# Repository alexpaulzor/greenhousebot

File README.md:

# greenhousebot

Controller for a greenhouse: temperature/humidity-driven **misters** (12 V valve),
**fans** (mains, switched externally) — an **exhaust/vent** fan and an **interior
circulation** fan on independent relays — and a **window** (12 V linear actuator via
H-bridge), on a **Raspberry Pi Pico 2 W** with a 1602 LCD + 3 buttons.

## Architecture (current)

- **Pico 2 W** brain; pre-made modules for relay / H-bridge / buck / LCD / AHT21 sensor.
- **No PCB — solderless terminal-block build.** The circuit is power-rail fan-out + a
  2-wire I2C bus, so a **Pico screw-terminal expander** + **Wago lever-nuts** do the
  interconnect. Nothing sensitive is soldered. See **[docs/WIRING.md](docs/WIRING.md)**.
- **Mains AC stays in mains-rated J-boxes**: a **3-channel 3.3 V relay board** (valve /
  vent fan / circ fan; mechanical, 10 A @ 125 V — no SSR) lives in a **relay J-box**, with a
  stacked **mains J-box** holding the incoming mains + two switched fan outlets. Only the
  relay coil side + the 12 V DC valve feed cross in from the logic box.
- **Single 12 V 5 A PSU** → valve + H-bridge + a buck to 5 V for the Pico.
- **Sensors**: **two AHT21** (I2C 0x38) — indoor (I2C0, with the LCD) + outdoor (I2C1, own
  bus, long run). **LCD run at 3.3 V** → whole I2C bus is 3.3 V, **no level shifter**.
- **Buttons**: three panel-mount momentaries; each press **cycles** its actuator's mode
  (window / fans / mister). Wire in via screw terminals.
- **Housing**: a purchased sealed plastic bin, mounted outdoors by the door, one gland.
  (Swappable LCD faceplate + MakerBeam module mounts are deferred TODOs.)

## Documents (start here)

| Doc | What |
|-----|------|
| [docs/CONNECTIONS.md](docs/CONNECTIONS.md) | **Logical pin-to-pin** (mermaid + table) — start here |
| [docs/WIRING.md](docs/WIRING.md) | **Solderless build guide** (buses, terminals, bring-up) |
| [docs/BOM.md](docs/BOM.md) | Bill of materials + sizing |
| [docs/PINOUT.md](docs/PINOUT.md) | Pico GPIO assignments (single source of truth) |
| [firmware/README.md](firmware/README.md) | **Firmware** modules, flashing, web API |

## Status

- [x] BOM finalized (2× AHT21, no level shifter, 12 V 5 A, terminal-block build)
- [x] Pin mappings finalized (two I2C buses for indoor + outdoor sensors)
- [x] Connectivity / circuit (logical) — `docs/CONNECTIONS.md`
- [x] Interconnect decided: **no PCB**, solderless terminal blocks — `docs/WIRING.md`
- [x] Firmware — button mode-cycles, LCD, LAN web control + scrape API, bounded flash
  datalog, **live automation** (per-actuator AUTO/manual modes driven by `control.py`),
  a **web chart** of the logged data, and **web-adjustable settings** (setpoints/timings
  tunable from the page, persisted to flash). 68 host tests passing. See `firmware/README.md`.

### Deferred TODOs
- Threshold **hysteresis** (deadbands) if the logs show actuator chatter at a setpoint.
- Laser-cut swappable LCD/button faceplate (1602 now, 2004 later).
- MakerBeam (15×15) module-mount plates.
- Confirm the window actuator's internal endstops (else use spare GP13/14/15).

---

## `pcb/` + `kicad/` — superseded PCB tooling (reference only)

An earlier direction was a milled single-sided carrier PCB. We **dropped the PCB** once
the parts became modular/socketed (a breakout is all that's needed). This tooling is kept
as a **learning artifact**, not part of the build:

- `pcb/*.py` — a from-scratch, reproducible PCB toolchain (footprints → placement →
  netlist → maze router → **polygon DRC gate** → GRBL post). The DRC refused to emit
  shorting G-code, which is what surfaced that a dense single-sided board was marginal.
- `kicad/greenhousebot.kicad_pcb` — a pcbnew-API-generated board. **Note:** it opens via
  the CLI/DRC but **crashes the KiCad GUI** because its custom Pico footprint isn't backed
  by a library table entry (a known limitation of API-built boards). Not worth fixing since
  the PCB is dropped; don't rely on these files for the build.

`CIRCUIT.md` and `KICAD_SETUP.md` document that earlier PCB path.

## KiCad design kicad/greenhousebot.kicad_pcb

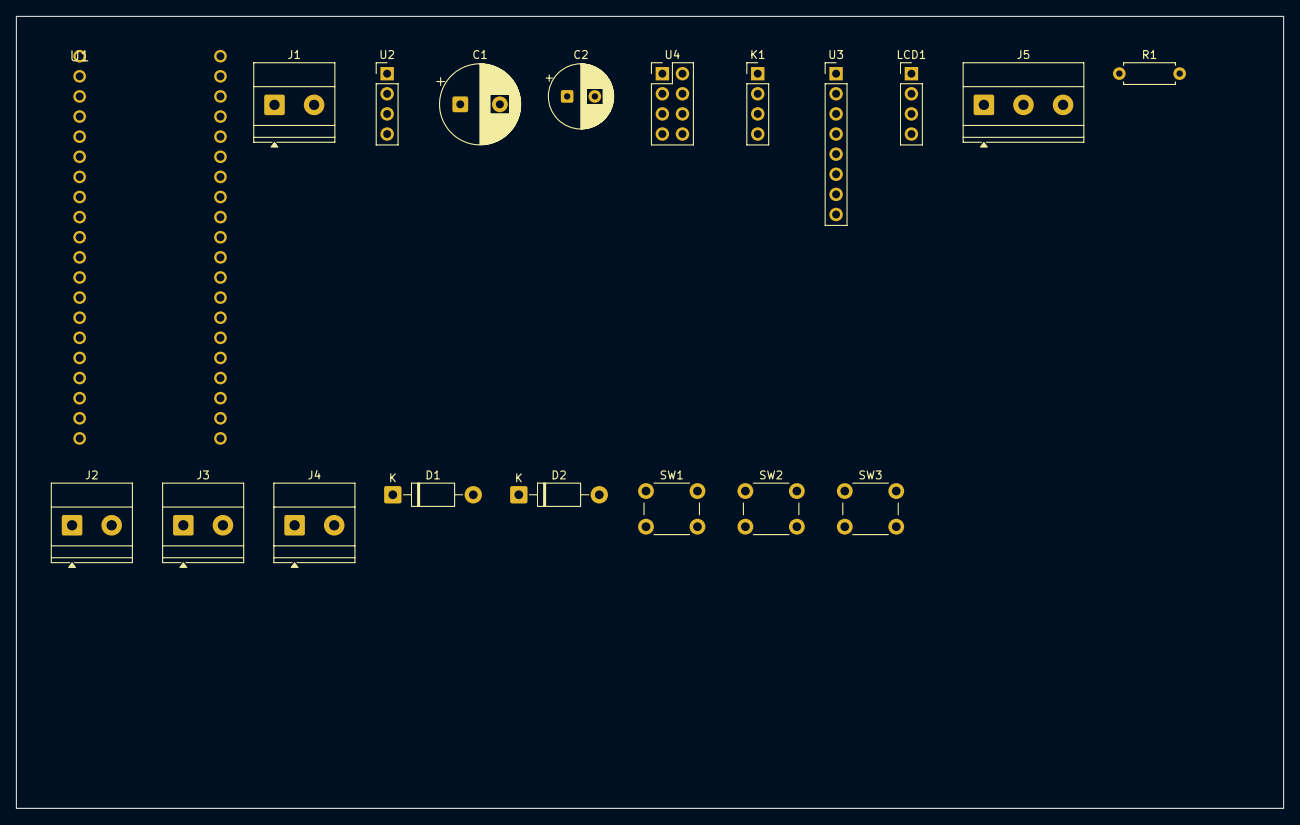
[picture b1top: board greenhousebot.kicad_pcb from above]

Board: 2 copper layers, 160.0 x 100.0 mm, 19 parts (0 on the bottom side), 20 nets, no tracks yet.

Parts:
C1: 1000uF; CP_Radial_D10.0mm_P5.00mm
C2: 470uF; CP_Radial_D8.0mm_P3.50mm
D1: SS14; D_DO-41_SOD81_P10.16mm_Horizontal
D2: 1N4007; D_DO-41_SOD81_P10.16mm_Horizontal
J1: 12V_IN; TerminalBlock_Phoenix_MKDS-1,5-2_1x02_P5.00mm_Horizontal
J2: VALVE; TerminalBlock_Phoenix_MKDS-1,5-2_1x02_P5.00mm_Horizontal
J3: ACTUATOR; TerminalBlock_Phoenix_MKDS-1,5-2_1x02_P5.00mm_Horizontal
J4: MAINS_TRIG; TerminalBlock_Phoenix_MKDS-1,5-2_1x02_P5.00mm_Horizontal
J5: DHT22; TerminalBlock_Phoenix_MKDS-1,5-3_1x03_P5.00mm_Horizontal
K1: Relay2ch; PinHeader_1x04_P2.54mm_Vertical
LCD1: LCD_I2C; PinHeader_1x04_P2.54mm_Vertical
R1: 10k; R_Axial_DIN0207_L6.3mm_D2.5mm_P7.62mm_Horizontal
SW1: BTN-; SW_PUSH_6mm
SW2: BTN_OK; SW_PUSH_6mm
SW3: BTN+; SW_PUSH_6mm
U1: Pico_2W
U2: Buck_5V; PinHeader_1x04_P2.54mm_Vertical
U3: BTS7960; PinHeader_1x08_P2.54mm_Vertical
U4: BSS138_LS; PinHeader_2x04_P2.54mm_Vertical

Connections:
3V3: J5.1, K1.1, R1.1, U1.36, U4.2
5V_BUCK: C2.1, D1.2, LCD1.2, U2.3, U4.5
5V_VSYS: D1.1, U1.39
12V: C1.1, J1.1, U2.1, U3.7
BTN_MINUS: SW1.1, U1.15
BTN_OK: SW2.1, U1.16
BTN_PLUS: SW3.1, U1.14
DHT_DATA: J5.2, R1.2, U1.20
GND: C1.2, C2.2, D2.2, J1.2, J2.2, J5.3, K1.4, LCD1.1, SW1.2, SW2.2, SW3.2, U1.3, U1.23, U1.38, U2.2, U2.4, U3.8, U4.1, U4.6
HB_EN: U1.26, U3.3, U3.4
HB_IS: U1.31, U3.5, U3.6
HB_LPWM: U1.25, U3.2
HB_RPWM: U1.24, U3.1
RLY1_IN: K1.2, U1.21
RLY2_IN: K1.3, U1.22
SCL_3V3: U1.7, U4.4
SCL_5V: LCD1.4, U4.8
SDA_3V3: U1.6, U4.3
SDA_5V: LCD1.3, U4.7
VALVE_SW: D2.1, J2.1
